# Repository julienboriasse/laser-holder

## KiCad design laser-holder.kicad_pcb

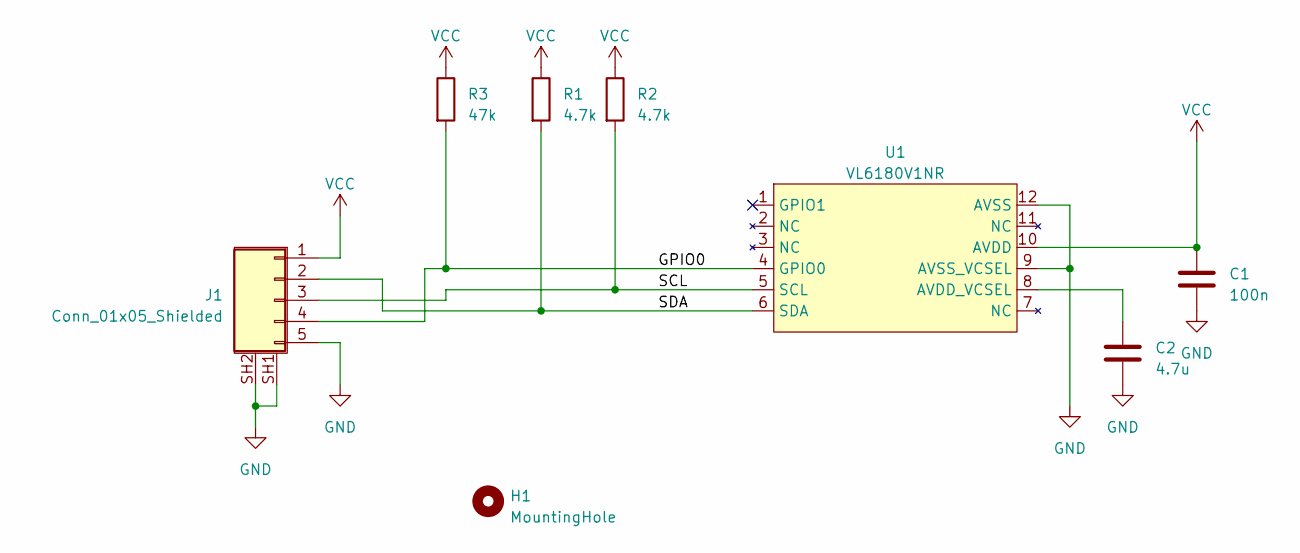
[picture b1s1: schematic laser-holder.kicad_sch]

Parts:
C1: 100n; C_0603_1608Metric_Pad1.08x0.95mm_HandSolder
C2: 4.7u; C_0603_1608Metric_Pad1.08x0.95mm_HandSolder
H1: MountingHole; MountingHole_2.2mm_M2
J1: Conn_01x05_Shielded; SAMTEC_T1M-05-F-SH-L
R1, R2: 4.7k; R_0603_1608Metric_Pad0.98x0.95mm_HandSolder
R3: 47k; R_0603_1608Metric_Pad0.98x0.95mm_HandSolder
U1: VL6180V1NR

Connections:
/GPIO0: J1.4, R3.2, U1.4 (GPIO0)
/SCL: J1.3, R2.2, U1.5 (SCL)
/SDA: J1.2, R1.2, U1.6 (SDA)
GND: C1.2, C2.2, J1.5, J1.SH1 (Shield), J1.SH2 (Shield), U1.9 (AVSS_VCSEL), U1.12 (AVSS)
unnamed: C2.1, U1.8 (AVDD_VCSEL)
VCC: C1.1, J1.1, R1.1, R2.1, R3.1, U1.10 (AVDD)

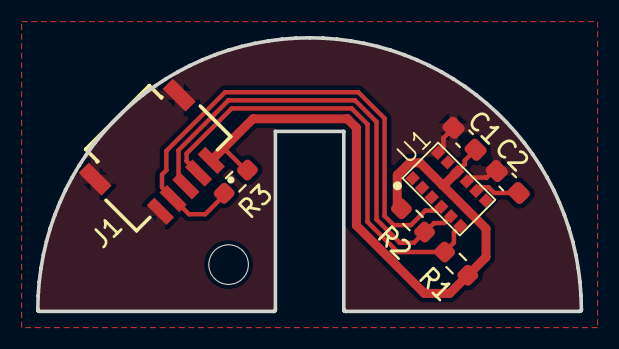
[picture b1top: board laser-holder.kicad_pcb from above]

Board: 2 copper layers, 30.2 x 15.2 mm, 8 parts (0 on the bottom side), 6 nets.
